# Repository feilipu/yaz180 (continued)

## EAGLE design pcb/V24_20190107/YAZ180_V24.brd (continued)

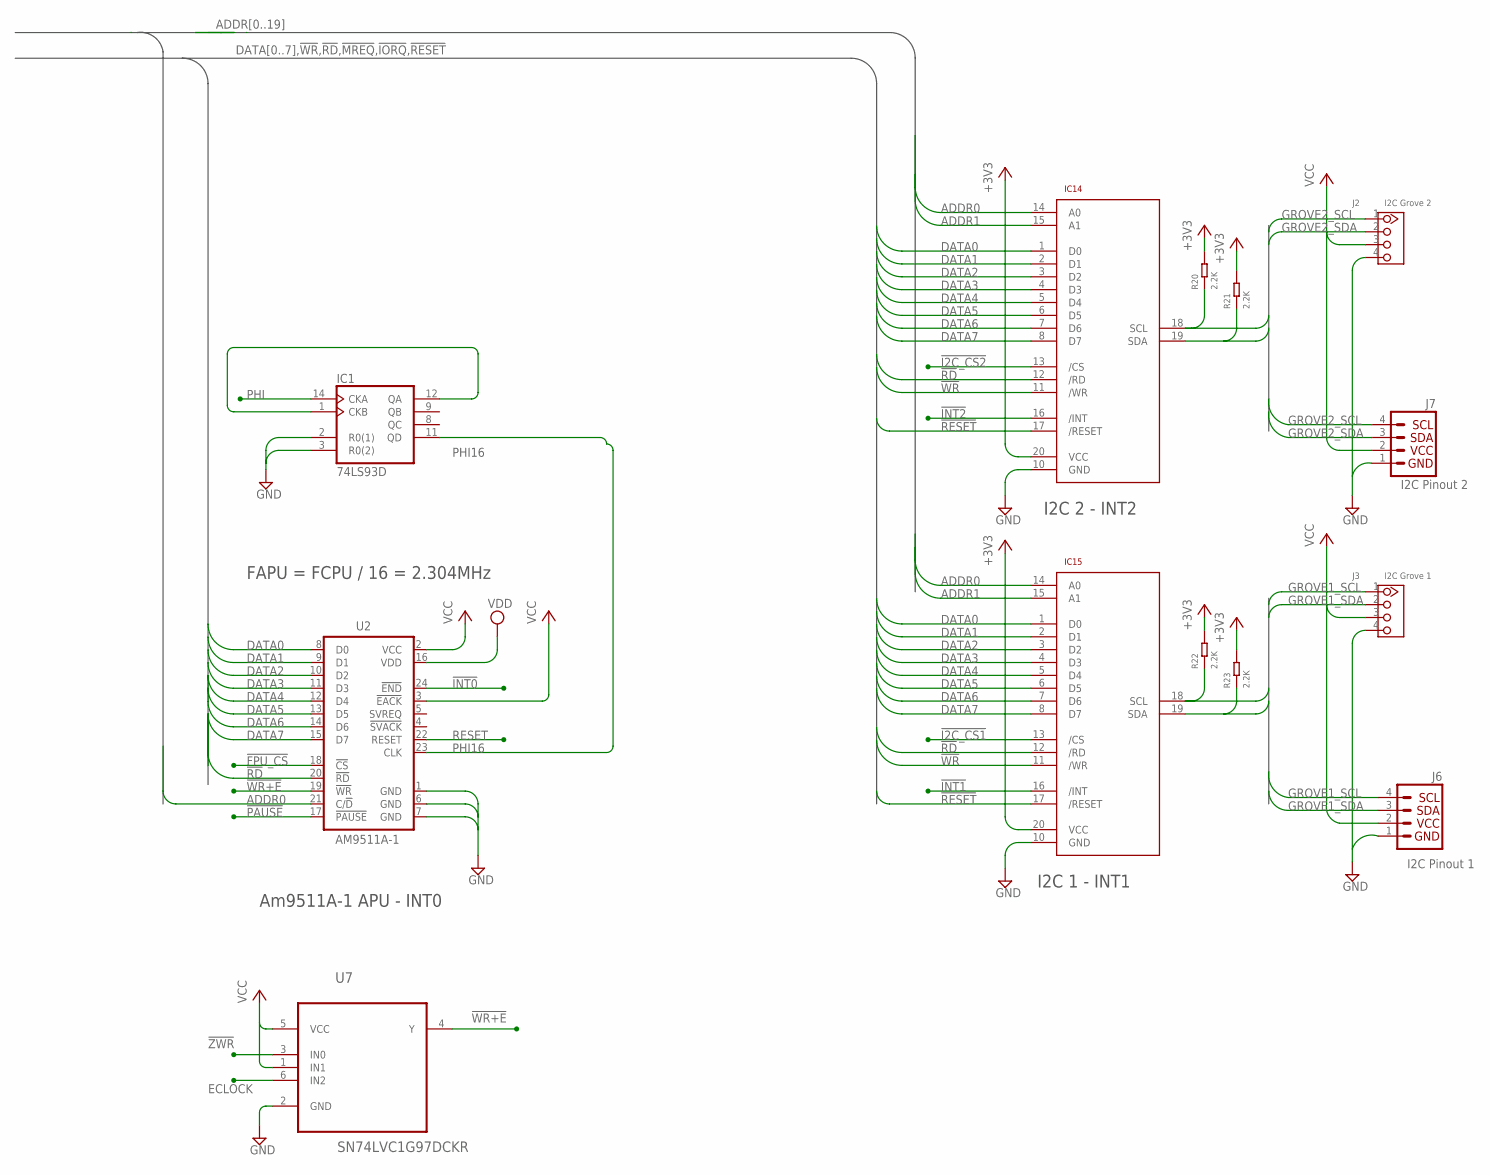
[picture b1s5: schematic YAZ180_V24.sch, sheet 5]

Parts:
IC1: 74LS93D; SO14
IC14, IC15: PCA9665; TSSOP20
J2: I2C Grove 2; HW4-2.0-90D
J3: I2C Grove 1; HW4-2.0-90D
J6: I2C Pinout 1; 1X04
J7: I2C Pinout 2; 1X04
R20, R21, R22, R23: 2.2K; R0603
U2: AM9511A-1; DIL24-6
U7: SN74LVC1G97DCKR; SOT65P210X110-6N

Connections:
!FPU_CS: U2.18 (!CS); also elsewhere on the board
!I2C_CS1: IC15.13 (/CS); also elsewhere on the board
!I2C_CS2: IC14.13 (/CS); also elsewhere on the board
!INT0: U2.24 (!END); also elsewhere on the board
!INT1: IC15.16 (/INT); also elsewhere on the board
!INT2: IC14.16 (/INT); also elsewhere on the board
!PAUSE: U2.17 (!PAUSE); also elsewhere on the board
!RD: IC14.12 (/RD), IC15.12 (/RD), U2.20 (!RD); also elsewhere on the board
!RESET: IC14.17 (/RESET), IC15.17 (/RESET); also elsewhere on the board
!WR: IC14.11 (/WR), IC15.11 (/WR); also elsewhere on the board
!WR+E: U2.19 (!WR), U7.4 (Y)
!ZWR: U7.3 (IN0); also elsewhere on the board
+3V3: IC14.20 (VCC), IC15.20 (VCC), R20.2, R21.2, R22.2, R23.2; also elsewhere on the board
ADDR0: IC14.14 (A0), IC15.14 (A0), U2.21 (C/!D); also elsewhere on the board
ADDR1: IC14.15 (A1), IC15.15 (A1); also elsewhere on the board
DATA0: IC14.1 (D0), IC15.1 (D0), U2.8 (D0); also elsewhere on the board
DATA1: IC14.2 (D1), IC15.2 (D1), U2.9 (D1); also elsewhere on the board
DATA2: IC14.3 (D2), IC15.3 (D2), U2.10 (D2); also elsewhere on the board
DATA3: IC14.4 (D3), IC15.4 (D3), U2.11 (D3); also elsewhere on the board
DATA4: IC14.5 (D4), IC15.5 (D4), U2.12 (D4); also elsewhere on the board
DATA5: IC14.6 (D5), IC15.6 (D5), U2.13 (D5); also elsewhere on the board
DATA6: IC14.7 (D6), IC15.7 (D6), U2.14 (D6); also elsewhere on the board
DATA7: IC14.8 (D7), IC15.8 (D7), U2.15 (D7); also elsewhere on the board
ECLOCK: U7.6 (IN2); also elsewhere on the board
GND: IC1.2 (R0(1)), IC1.3 (R0(2)), IC1.10 (GND), IC14.10 (GND), IC15.10 (GND), J2.4, J3.4, J6.1, J7.1, U2.1 (GND), U2.6 (GND), U2.7 (GND), U7.2 (GND); also elsewhere on the board
GROVE1_SCL: IC15.18 (SCL), J3.1, J6.4, R22.1
GROVE1_SDA: IC15.19 (SDA), J3.2, J6.3, R23.1
GROVE2_SCL: IC14.18 (SCL), J2.1, J7.4, R20.1
GROVE2_SDA: IC14.19 (SDA), J2.2, J7.3, R21.1
unnamed: IC1.1 (CKB), IC1.12 (QA)
PHI: IC1.14 (CKA); also elsewhere on the board
PHI16: IC1.11 (QD), U2.23 (CLK)
RESET: U2.22 (RESET); also elsewhere on the board
VCC: IC1.5 (VCC), J2.3, J3.3, J6.2, J7.2, U2.2 (VCC), U2.3 (!EACK), U7.1 (IN1), U7.5 (VCC); also elsewhere on the board
VDD: U2.16 (VDD); also elsewhere on the board

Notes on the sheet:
Am9511A-1 APU - INT0
I2C 2 - INT2
I2C 1 - INT1
FAPU = FCPU / 16 = 2.304MHz

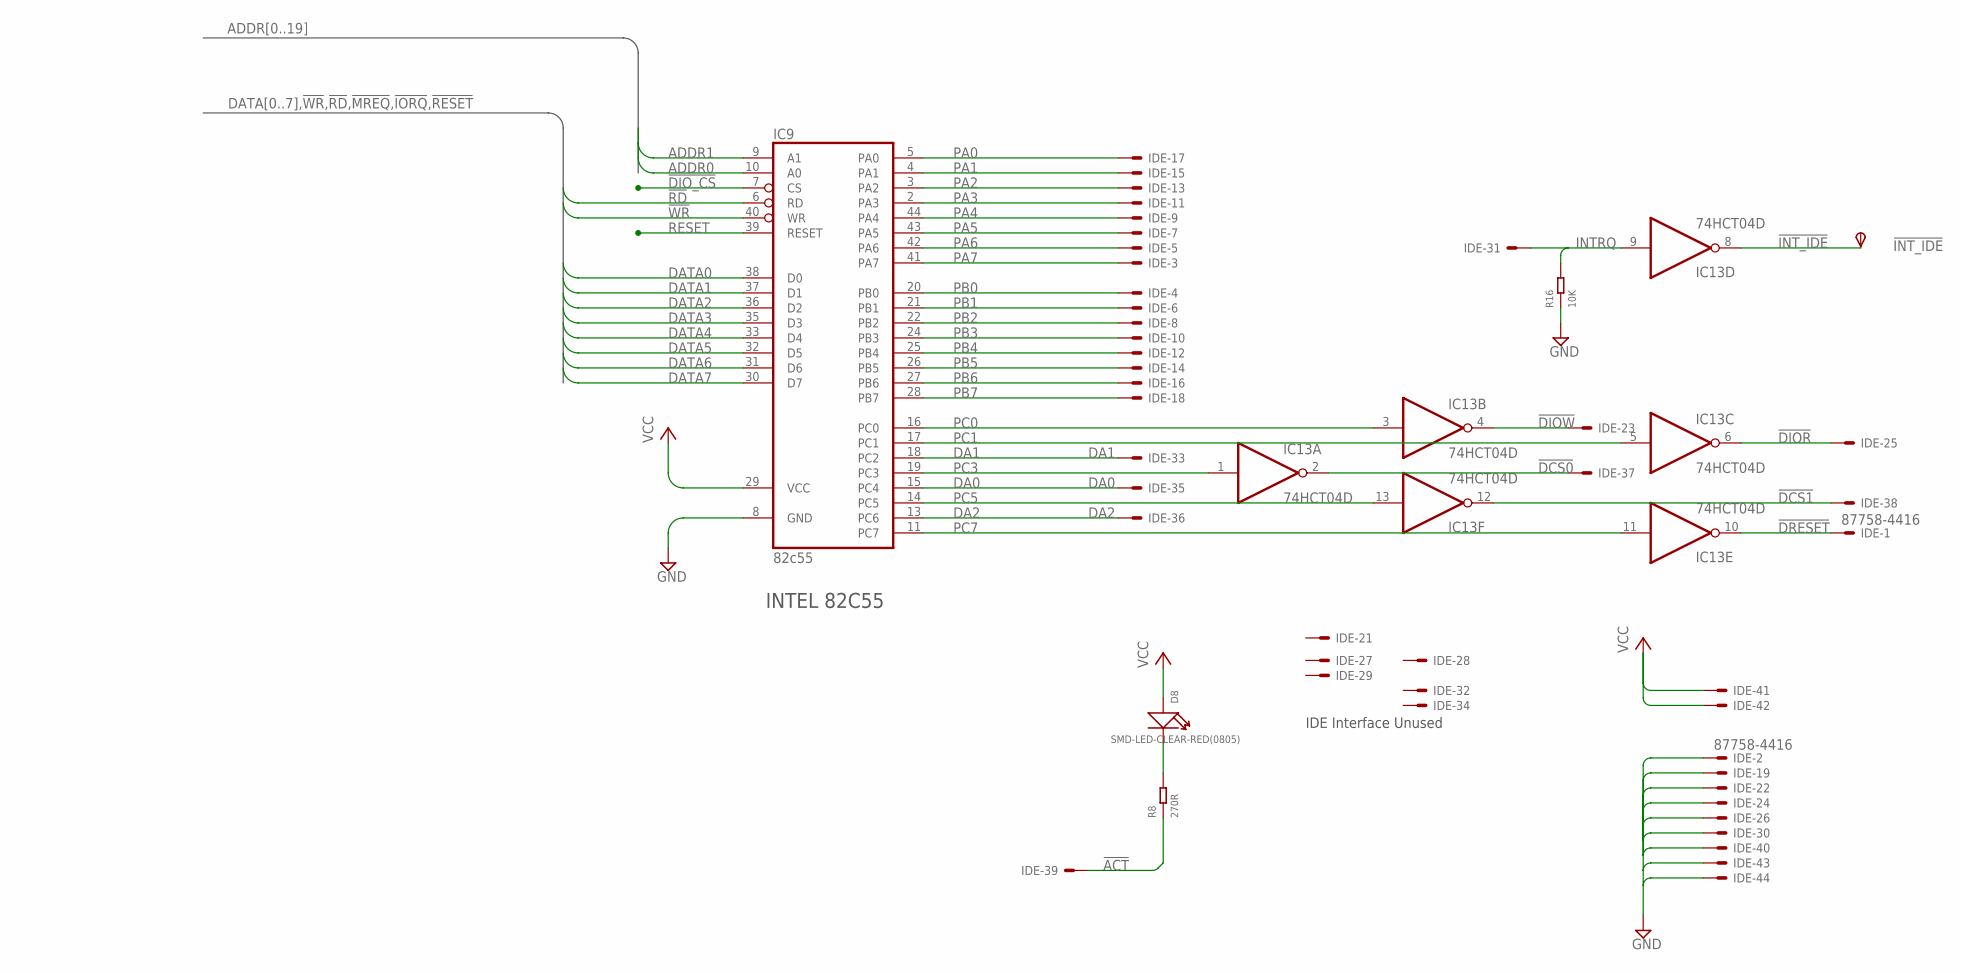
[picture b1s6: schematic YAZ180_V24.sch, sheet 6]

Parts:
!INT_IDE: TPSPAD1-13; P1-13
D8: SMD-LED-CLEAR-RED(0805); LED-0805
IC9: 82c55; S44
IC13: 74HCT04D; SO14
IDE: 87758-4416
R8: 270R; R0603
R16: 10K; R0603

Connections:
!ACT: IDE.39, R8.1
!DCS0: IC13.2 (O), IDE.37
!DCS1: IC13.12 (O), IDE.38
!DIOR: IC13.6 (O), IDE.25
!DIOW: IC13.4 (O), IDE.23
!DIO_CS: IC9.7 (CS); also elsewhere on the board
!DRESET: IC13.10 (O), IDE.1
!INT_IDE: !INT_IDE.TP, IC13.8 (O)
!RD: IC9.6 (RD); also elsewhere on the board
!WR: IC9.40 (WR); also elsewhere on the board
ADDR0: IC9.10 (A0); also elsewhere on the board
ADDR1: IC9.9 (A1); also elsewhere on the board
DA0: IC9.15 (PC4), IDE.35
DA1: IC9.18 (PC2), IDE.33
DA2: IC9.13 (PC6), IDE.36
DATA0: IC9.38 (D0); also elsewhere on the board
DATA1: IC9.37 (D1); also elsewhere on the board
DATA2: IC9.36 (D2); also elsewhere on the board
DATA3: IC9.35 (D3); also elsewhere on the board
DATA4: IC9.33 (D4); also elsewhere on the board
DATA5: IC9.32 (D5); also elsewhere on the board
DATA6: IC9.31 (D6); also elsewhere on the board
DATA7: IC9.30 (D7); also elsewhere on the board
GND: IC9.8 (GND), IC13.7 (GND), IDE.2, IDE.19, IDE.22, IDE.24, IDE.26, IDE.30, IDE.40, IDE.43, IDE.44, R16.1; also elsewhere on the board
INTRQ: IC13.9 (I), IDE.31, R16.2
unnamed: D8.-, R8.2
PA0: IC9.5 (PA0), IDE.17
PA1: IC9.4 (PA1), IDE.15
PA2: IC9.3 (PA2), IDE.13
PA3: IC9.2 (PA3), IDE.11
PA4: IC9.44 (PA4), IDE.9
PA5: IC9.43 (PA5), IDE.7
PA6: IC9.42 (PA6), IDE.5
PA7: IC9.41 (PA7), IDE.3
PB0: IC9.20 (PB0), IDE.4; also elsewhere on the board
PB1: IC9.21 (PB1), IDE.6; also elsewhere on the board
PB2: IC9.22 (PB2), IDE.8; also elsewhere on the board
PB3: IC9.24 (PB3), IDE.10; also elsewhere on the board
PB4: IC9.25 (PB4), IDE.12; also elsewhere on the board
PB5: IC9.26 (PB5), IDE.14; also elsewhere on the board
PB6: IC9.27 (PB6), IDE.16; also elsewhere on the board
PB7: IC9.28 (PB7), IDE.18; also elsewhere on the board
PC0: IC9.16 (PC0), IC13.3 (I)
PC1: IC9.17 (PC1), IC13.5 (I); also elsewhere on the board
PC3: IC9.19 (PC3), IC13.1 (I)
PC5: IC9.14 (PC5), IC13.13 (I)
PC7: IC9.11 (PC7), IC13.11 (I)
RESET: IC9.39 (RESET); also elsewhere on the board
VCC: D8.+, IC9.29 (VCC), IC13.14 (VCC), IDE.41, IDE.42; also elsewhere on the board

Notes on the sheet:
INTEL 82C55
IDE Interface Unused

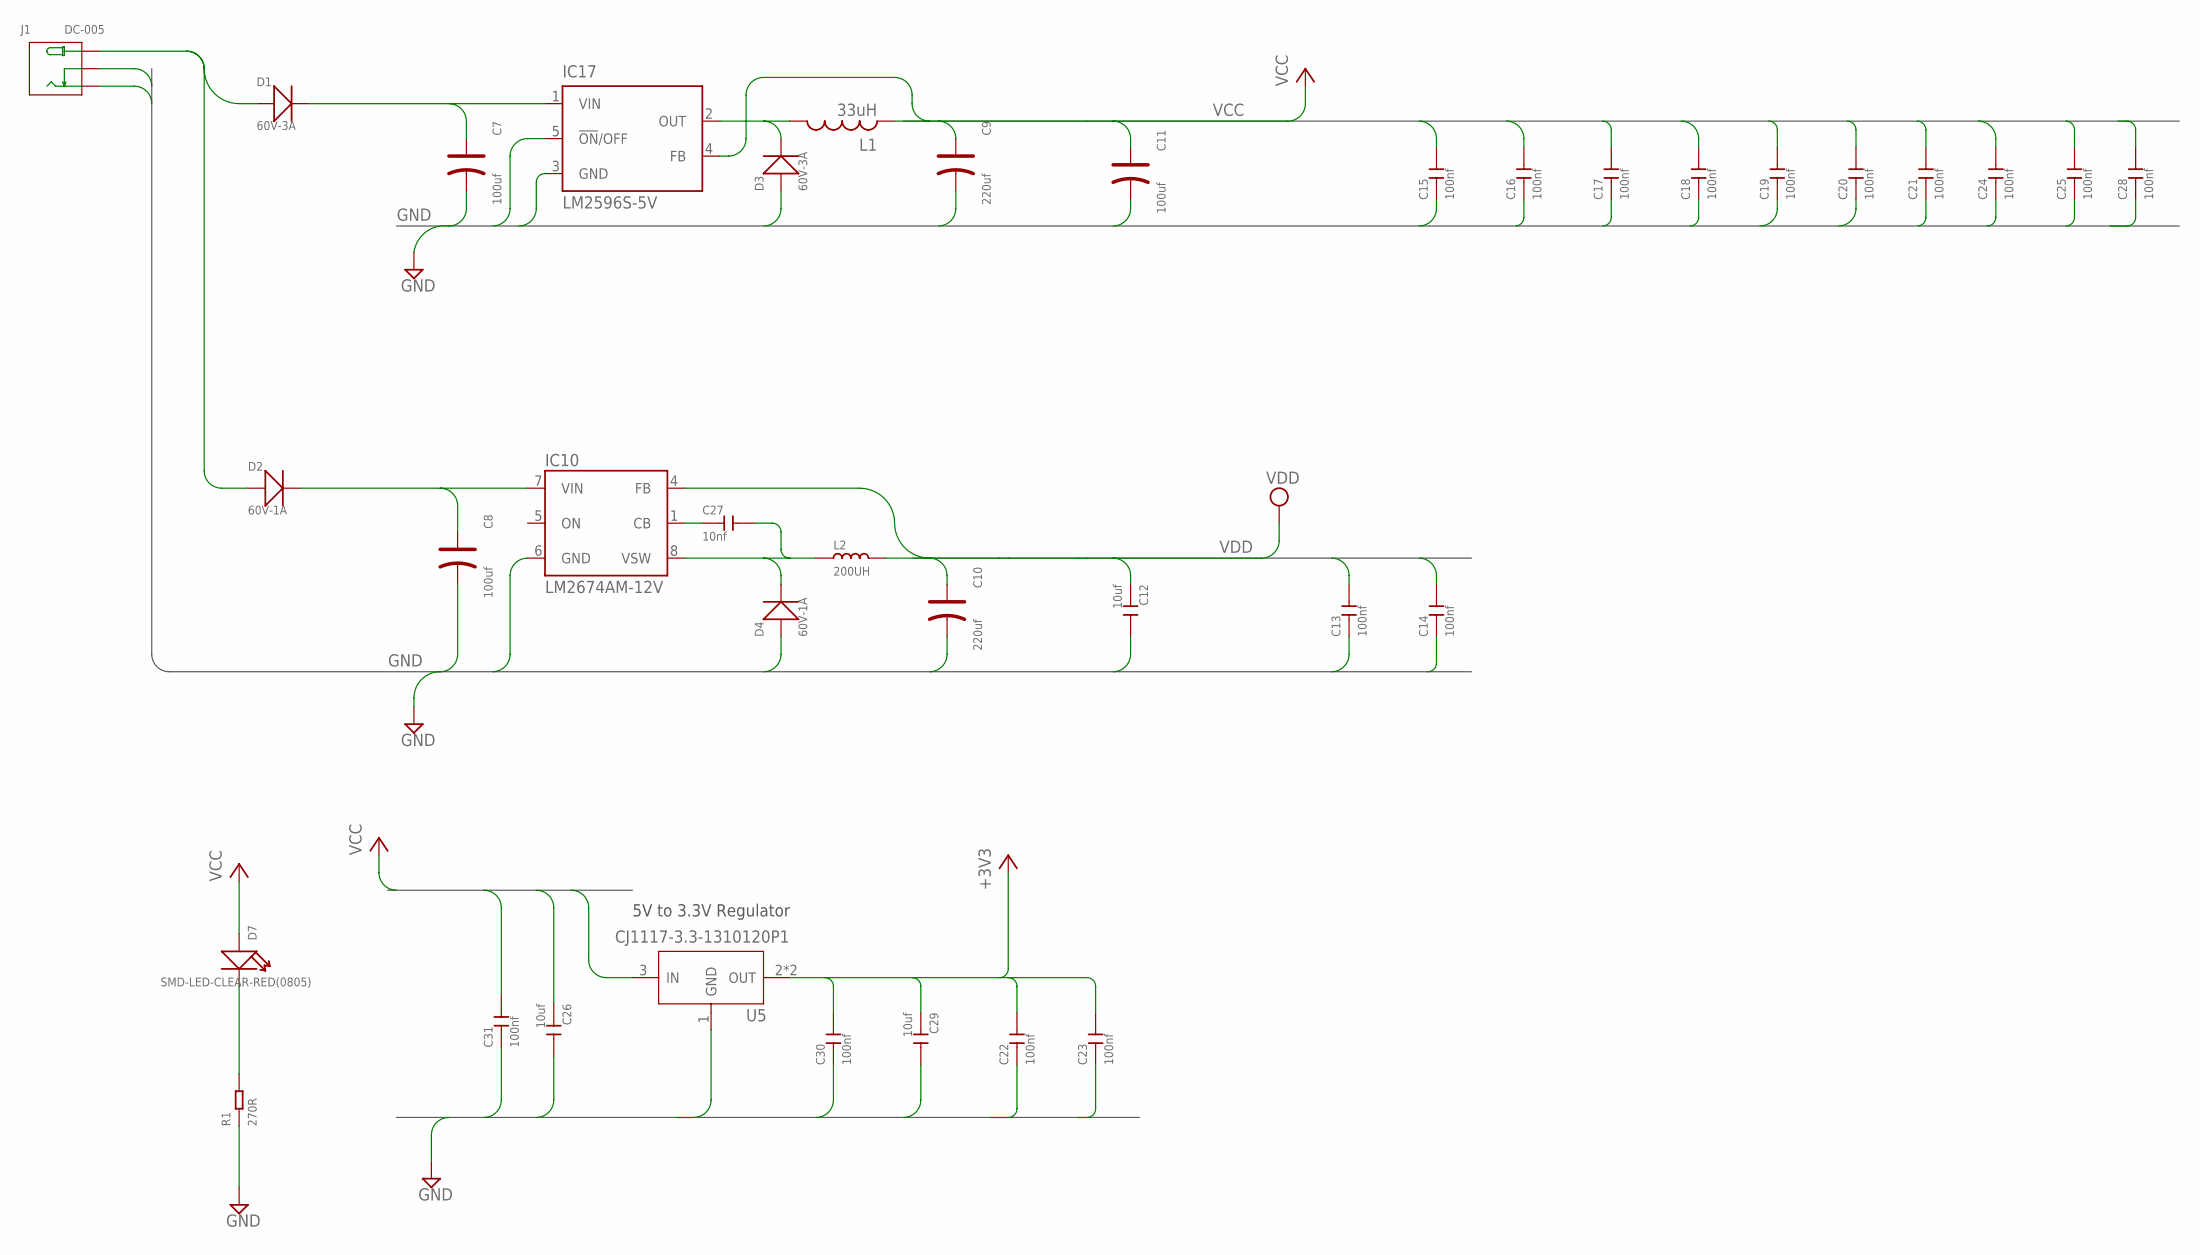
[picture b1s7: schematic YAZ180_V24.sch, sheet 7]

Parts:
C7, C8: 100uf; ELECTRO-SMD-E-7.8MM
C9, C10: 220uf; AVX-E
C11: 100uf; AVX-C
C12, C26, C29: 10uf; C0805
C13, C14, C15, C16, C17, C18, C19, C20, C21, C22, C23, C24, C25, C28, C30, C31: 100nf; C0603
C27: 10nf; C0603
D1, D3: 60V-3A; SOD-323
D2, D4: 60V-1A; SOD-323
D7: SMD-LED-CLEAR-RED(0805); LED-0805
IC10: LM2674AM-12V; SO08
IC17: LM2596S-5V; TO263-5
J1: DC-005; DCJ3P-14.2X11.0X9.0MM
L1: 33uH; MSS1260
L2: 200UH; SMD-2P-5.0X5.0X2.0MM
R1: 270R; R0603
U5: CJ1117-3.3-1310120P1; SOT89

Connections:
+3V3: C22.2, C23.2, C29.1, C30.2, U5.2 (OUT), U5.4 (OUT); also elsewhere on the board
GND: C7.-, C8.-, C9.-, C10.-, C11.-, C12.2, C13.1, C14.1, C15.1, C16.1, C17.1, C18.1, C19.1, C20.1, C21.1, C22.1, C23.1, C24.1, C25.1, C26.2, C28.1, C29.2, C30.1, C31.1, D3.+, D4.+, IC10.6 (GND), IC17.3 (GND), IC17.5 (!ON!/OFF), J1.-1 (-), J1.-2 (CDN), R1.1, U5.1 (GND); also elsewhere on the board
unnamed: C27.1, IC10.1 (CB)
unnamed: D1.+, D2.+, J1.+
unnamed: D7.-, R1.2
unnamed: C7.+, D1.-, IC17.1 (VIN)
unnamed: C8.+, D2.-, IC10.7 (VIN)
unnamed: D3.-, IC17.2 (OUT), L1.P$1
unnamed: C27.2, D4.-, IC10.8 (VSW), L2.1
VCC: C9.+, C11.+, C15.2, C16.2, C17.2, C18.2, C19.2, C20.2, C21.2, C24.2, C25.2, C26.1, C28.2, C31.2, D7.+, IC17.4 (FB), L1.P$2, U5.3 (IN); also elsewhere on the board
VDD: C10.+, C12.1, C13.2, C14.2, IC10.4 (FB), L2.2; also elsewhere on the board

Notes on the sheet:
5V to 3.3V Regulator

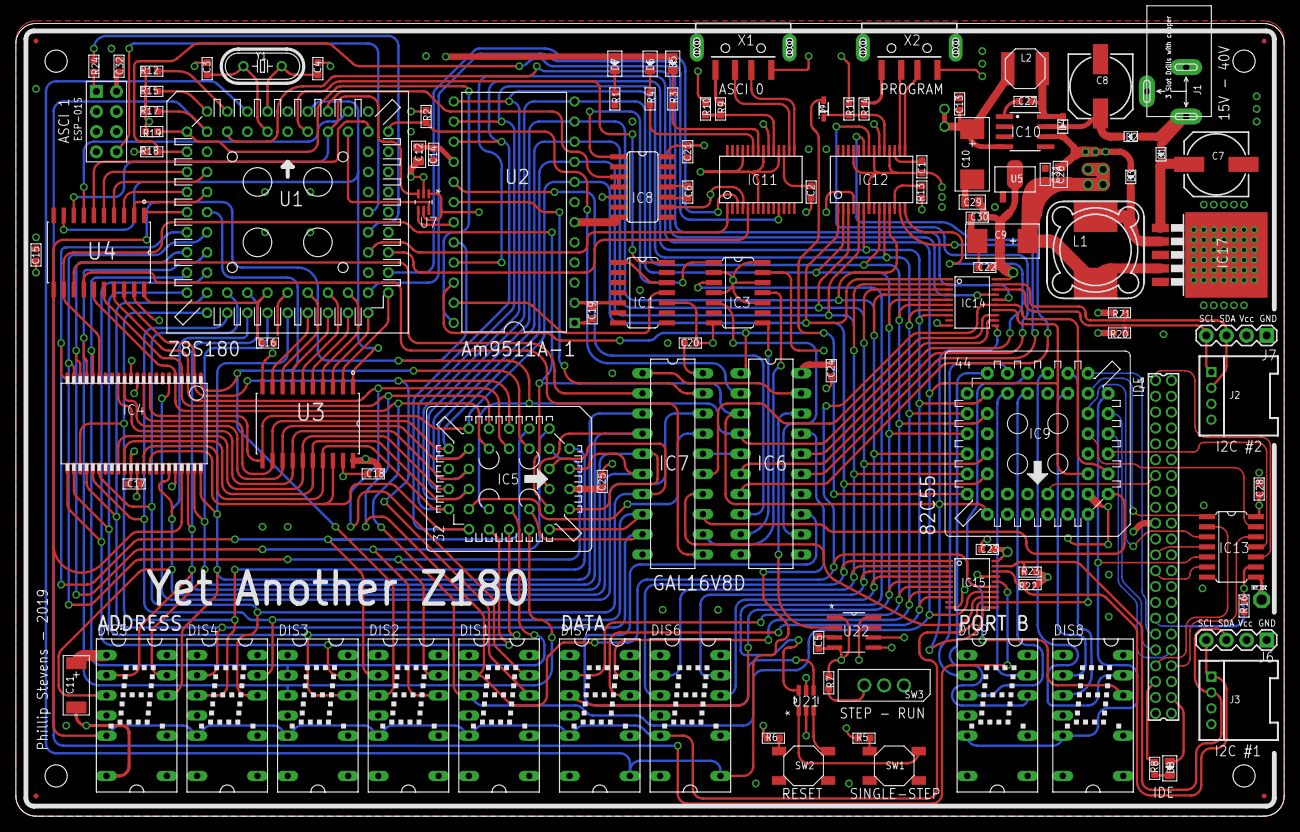
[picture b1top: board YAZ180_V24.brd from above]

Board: 4 copper layers, 160.0 x 100.0 mm, 117 parts (0 on the bottom side), 163 nets.

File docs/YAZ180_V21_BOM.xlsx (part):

Part | Value | Device | Package | Description | MF | MPN | OC_FARNELL | OC_NEWARK | PACKAGE | SUPPLIER | TP_SIGNAL_NAME | VALUE
!INT_IDE | TPSPAD1-13 | TPSPAD1-13 | P1-13 | TEST PIN
C1 | 100nf | CERAMIC-100NF-50V-10%-X7R(0603) | C0603 | 302010138 |  | CC0603KRX7R9BB104 |  |  |  |  |  | 100nf
C2 | 100nf | CERAMIC-100NF-50V-10%-X7R(0603) | C0603 | 302010138 |  | CC0603KRX7R9BB104 |  |  |  |  |  | 100nf
C3 | 22pf | CERAMIC-22PF-50V-5%-NPO(0603) | C0603 | 302010143 |  |  |  |  |  |  |  | 22pf
C4 | 22pf | CERAMIC-22PF-50V-5%-NPO(0603) | C0603 | 302010143 |  |  |  |  |  |  |  | 22pf
C5 | 2.2uf | CERAMIC-2.2UF-10V-10%-X7R(0603) | C0603 | 302010054 |  | CC0603KRX7R6BB225 |  |  |  |  |  | 2.2uf
C6 | 22pf | CERAMIC-22PF-50V-5%-NPO(0603) | C0603 | 302010143 |  |  |  |  |  |  |  | 22pf
C7 | 100uf | ALUMINUM-SMD-100UF-50V(D8-H10.5MM) | ELECTRO-SMD-E-7.8MM | 302030095 |  | CS1H101M-CRF10 |  |  |  |  |  | 100uf
C8 | 100uf | ALUMINUM-SMD-100UF-50V(D8-H10.5MM) | ELECTRO-SMD-E-7.8MM | 302030095 |  | CS1H101M-CRF10 |  |  |  |  |  | 100uf
C9 | 220uf | TANTALUM-SMD-220UF-16V(AVX-E) | AVX-E | 302020032 |  | TAJE227K016RNJ |  |  |  |  |  | 220uf
C10 | 220uf | TANTALUM-SMD-220UF-16V(AVX-E) | AVX-E | 302020032 |  | TAJE227K016RNJ |  |  |  |  |  | 220uf
C11 | 100uf | TANTALUM-SMD-100UF-16V(AVX-C) | AVX-C | 302020023 |  | TAJC107K016RNJ |  |  |  |  |  | 100uf
C12 | 10uf | CERAMIC-10UF-25V-10%-X5R(0805) | C0805 | 302010178 |  | CC0805KKX5R8BB106 |  |  |  |  |  | 10uf
C13 | 100nf | CERAMIC-100NF-50V-10%-X7R(0603) | C0603 | 302010138 |  | CC0603KRX7R9BB104 |  |  |  |  |  | 100nf
C14 | 100nf | CERAMIC-100NF-50V-10%-X7R(0603) | C0603 | 302010138 |  | CC0603KRX7R9BB104 |  |  |  |  |  | 100nf
C15 | 100nf | CERAMIC-100NF-50V-10%-X7R(0603) | C0603 | 302010138 |  | CC0603KRX7R9BB104 |  |  |  |  |  | 100nf
C16 | 100nf | CERAMIC-100NF-50V-10%-X7R(0603) | C0603 | 302010138 |  | CC0603KRX7R9BB104 |  |  |  |  |  | 100nf
C17 | 100nf | CERAMIC-100NF-50V-10%-X7R(0603) | C0603 | 302010138 |  | CC0603KRX7R9BB104 |  |  |  |  |  | 100nf
C18 | 100nf | CERAMIC-100NF-50V-10%-X7R(0603) | C0603 | 302010138 |  | CC0603KRX7R9BB104 |  |  |  |  |  | 100nf
C19 | 100nf | CERAMIC-100NF-50V-10%-X7R(0603) | C0603 | 302010138 |  | CC0603KRX7R9BB104 |  |  |  |  |  | 100nf
C20 | 100nf | CERAMIC-100NF-50V-10%-X7R(0603) | C0603 | 302010138 |  | CC0603KRX7R9BB104 |  |  |  |  |  | 100nf
C21 | 100nf | CERAMIC-100NF-50V-10%-X7R(0603) | C0603 | 302010138 |  | CC0603KRX7R9BB104 |  |  |  |  |  | 100nf
C22 | 100nf | CERAMIC-100NF-50V-10%-X7R(0603) | C0603 | 302010138 |  | CC0603KRX7R9BB104 |  |  |  |  |  | 100nf
C23 | 100nf | CERAMIC-100NF-50V-10%-X7R(0603) | C0603 | 302010138 |  | CC0603KRX7R9BB104 |  |  |  |  |  | 100nf
C24 | 100nf | CERAMIC-100NF-50V-10%-X7R(0603) | C0603 | 302010138 |  | CC0603KRX7R9BB104 |  |  |  |  |  | 100nf
C25 | 100nf | CERAMIC-100NF-50V-10%-X7R(0603) | C0603 | 302010138 |  | CC0603KRX7R9BB104 |  |  |  |  |  | 100nf
C26 | 10uf | CERAMIC-10UF-25V-10%-X5R(0805) | C0805 | 302010178 |  | CC0805KKX5R8BB106 |  |  |  |  |  | 10uf
C27 | 10nf | CERAMIC-10NF-50V-10%-X7R(0603) | C0603 | 302010140 |  | CC0603KRX7R9BB103 |  |  |  |  |  | 10nf
C28 | 100nf | CERAMIC-100NF-50V-10%-X7R(0603) | C0603 | 302010138 |  | CC0603KRX7R9BB104 |  |  |  |  |  | 100nf
C29 | 10uf | CERAMIC-10UF-25V-10%-X5R(0805) | C0805 | 302010178 |  | CC0805KKX5R8BB106 |  |  |  |  |  | 10uf
C30 | 100nf | CERAMIC-100NF-50V-10%-X7R(0603) | C0603 | 302010138 |  | CC0603KRX7R9BB104 |  |  |  |  |  | 100nf
C31 | 100nf | CERAMIC-100NF-50V-10%-X7R(0603) | C0603 | 302010138 |  | CC0603KRX7R9BB104 |  |  |  |  |  | 100nf
C32 | 100nf | CERAMIC-100NF-50V-10%-X7R(0603) | C0603 | 302010138 |  | CC0603KRX7R9BB104 |  |  |  |  |  | 100nf
C33 | 100nf | CERAMIC-100NF-50V-10%-X7R(0603) | C0603 | 302010138 |  | CC0603KRX7R9BB104 |  |  |  |  |  | 100nf
D1 | 60V-3A | SMD-DIODE-SCHOTTKY-60V-1A(SOD-323) | SOD-323 | 304020026 |  | PMEG6010CEJ,115 |  |  |  |  |  | 60V-1A
D2 | 60V-1A | SMD-DIODE-SCHOTTKY-60V-1A(SOD-323) | SOD-323 | 304020026 |  | PMEG6010CEJ,115 |  |  |  |  |  | 60V-1A
D3 | 60V-3A | SMD-DIODE-SCHOTTKY-60V-1A(SOD-323) | SOD-323 | 304020026 |  | PMEG6010CEJ,115 |  |  |  |  |  | 60V-1A
D4 | 60V-1A | SMD-DIODE-SCHOTTKY-60V-1A(SOD-323) | SOD-323 | 304020026 |  | PMEG6010CEJ,115 |  |  |  |  |  | 60V-1A
D5 | SMD-LED-CLEAR-YELLOW(0805) | SMD-LED-CLEAR-YELLOW(0805) | LED-0805 | 304090039 |  | 17-215UYC/S530-A3/TR8
D6 | SMD-LED-CLEAR-GREEN(0805) | SMD-LED-CLEAR-GREEN(0805) | LED-0805 | 304090057 |  | 17-215SYGC/S530-E2/TR8
D7 | SMD-LED-CLEAR-RED(0805) | SMD-LED-CLEAR-RED(0805) | LED-0805 | 304090046 |  | 17-215SURC/S530-A2/TR8
D8 | SMD-LED-CLEAR-RED(0805) | SMD-LED-CLEAR-RED(0805) | LED-0805 | 304090046 |  | 17-215SURC/S530-A2/TR8
DIS1 | HTIL311A | HTIL311A | HTIL311A | LED DISPLAY 1-character dot matrix, 2 decimal points |  |  | unknown | unknown
DIS2 | HTIL311A | HTIL311A | HTIL311A | LED DISPLAY 1-character dot matrix, 2 decimal points |  |  | unknown | unknown
DIS3 | HTIL311A | HTIL311A | HTIL311A | LED DISPLAY 1-character dot matrix, 2 decimal points |  |  | unknown | unknown
DIS4 | HTIL311A | HTIL311A | HTIL311A | LED DISPLAY 1-character dot matrix, 2 decimal points |  |  | unknown | unknown
DIS5 | HTIL311A | HTIL311A | HTIL311A | LED DISPLAY 1-character dot matrix, 2 decimal points |  |  | unknown | unknown
DIS6 | HTIL311A | HTIL311A | HTIL311A | LED DISPLAY 1-character dot matrix, 2 decimal points |  |  | unknown | unknown
DIS7 | HTIL311A | HTIL311A | HTIL311A | LED DISPLAY 1-character dot matrix, 2 decimal points |  |  | unknown | unknown
DIS8 | HTIL311A | HTIL311A | HTIL311A | LED DISPLAY 1-character dot matrix, 2 decimal points |  |  | unknown | unknown
DIS9 | HTIL311A | HTIL311A | HTIL311A | LED DISPLAY 1-character dot matrix, 2 decimal points |  |  | unknown | unknown
ESP-01S | ESP-01S | DIP-BLACK-FEMALE-HEADER(2X4P-2.54) | H2X4-2.54 | 320030087 |  |  |  |  |  |  |  | 2X4P-2.54
IC1 | 74LS93D | 74LS93D | SO14 | Decade, divide by twelve and binary COUNTER
IC3 | 74ACT74D | 74ACT74D | SO14 | Dual D type positive edge triggered FLIP FLOP, preset and clear
IC4 | IS62WV10248DALL-55T | IS62WV10248DALL-55T | TSOP-II-44 | 1024k x 8 low voltage, ultra low power CMOS static RAM
IC5 | SST39VF010 | SST39VF010 | S32 | 1 Mbit x8 Multi-Purpose Flash
IC6 | ATF16V8BP3 | ATF16V8BP3 | DIL20 | High perfomance CMOS (electrically erasable) programmable logic device (PLD) |  | ATF16V8CZ-15PU | 1551768 | 94M6254
IC7 | ATF16V8BP3 | ATF16V8BP3 | DIL20 | High perfomance CMOS (electrically erasable) programmable logic device (PLD) |  | ATF16V8CZ-15PU | 1551768 | 94M6254
IC8 | 74121D | 74121D | SO14 | Monostable MULTIVIBRATOR, schmitt trigger inputs
IC9 | 82c55 | 82C55APLCC44-S | S44 | MICROCOMPUTER/PERIPHERAL DEVICE
IC10 | LM2674AM-12V | LM2674AM | SO08 | National Semiconductor 0.5A Simple Switcher"(c)"
IC11 | FT232RL | FT232RL | SSOP28DB | USB UART
IC12 | FT245RL | FT245RL | SSOP28DB | USB FIFO Controller
IC13 | 74HCT04D | 74HCT04D | SO14 | Hex INVERTER
IC14 | PCA9665 | PCA9665 | TSSOP20 | IC CNTRLR PARALLEL/I2C 20TSSOP
IC15 | PCA9665 | PCA9665 | TSSOP20 | IC CNTRLR PARALLEL/I2C 20TSSOP
IC17 | LM2596S-5V | LM2596S | TO263-5 | SIMPLE SWITCHERÂ® Power Converter 150 kHz 3A Step-Down Voltage Regulator | NATIONAL SEMICONDUCTOR | LM2596S-ADJ/NOPB | 9494367 | 41K3842
IDE | 87758-4416 | 87758-4416 | 87758-4416 | 44 Pin - 2mm Dual Row Single Wafer, Vertical T/H HDR | MOLEX | 87758-4416 | unknown | 59J1588
J1 | DC-005 | CONN-POWER-JACK-2.1MM(DC-005) | DCJ3P-14.2X11.0X9.0MM | 320120003 |  | DC-005 |  |  |  |  |  | DC-005
J2 | I2C Grove 2 | GROVE-CONNECTOR-DIP-90D(4P-2.0) | HW4-2.0-90D | 320110034
J3 | I2C Grove 1 | GROVE-CONNECTOR-DIP-90D(4P-2.0) | HW4-2.0-90D | 320110034
J6 | I2C Pinout 1 | I2C_STANDARD | 1X04 | SparkFun has standardized on a pinout for all I2C based sensor breakouts.
J7 | I2C Pinout 2 | I2C_STANDARD | 1X04 | SparkFun has standardized on a pinout for all I2C based sensor breakouts.
L1 | 33uH | MSS1260 | MSS1260 | SMT Power Inductor
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
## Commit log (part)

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2017-10-13 initial structure + documents
2017-10-13 add APU and update readme
2017-10-13 add readme image refs
2017-10-13 update docs memory & page 0
2017-10-13 update doc page 0
2017-10-15 yabios readme
2017-10-16 yabios readme.md update
2017-10-17 squash CA1 to 4kB
2017-10-18 remove double underscore
2017-10-23 implementation notes
2017-10-26 rethink bank address implementation
2017-10-26 update readme with far improvements
2017-10-29 update readme & notes
2017-10-29 update Page0 doc
2017-10-29 rename _memcpy_far & _memset_far
2017-10-30 revise memcpy_far and memset_far definitions
2017-10-31 Excel Version of BOM
    Includes stock in hand on 1 Nov 2017
2017-10-31 Digikey Shopping Cart
    Final V2.1 shopping cart at Digikey.
    In case the Internet forgets.
2017-10-31 readme updates
2017-11-01 initial yash implementation
2017-11-01 wip - CLI mostly done
2017-11-02 wip - shell complete excluding bank functions
2017-11-02 wip - check more boxes
2017-11-02 CLI is alive
2017-11-02 wip - last before banked integration
2017-11-03 mkb & mvb
2017-11-07 Working State - Melbourne Cup
2017-11-18 update images and readme
2017-11-18 update Tindie link
2017-11-18 add Tindie badge
2017-11-19 WIP - add perl z180tool
2017-11-25 create yabios.rex for API
2017-11-26 recompile with zsdcc 10186
2017-11-27 updates, compiling with zsdcc-9958
2017-11-30 halved Tx buffer size
2017-12-10 cpm22 ccp+bdos initial commit
2017-12-15 Update README.MD
    CP/M tick-box
2017-12-15 move IDE support to Common Area 1 for CP/M
2017-12-16 yabios03 hex file
2018-01-13 yabios CP/M WIP
2018-01-13 yabios CP/M WIP2
2018-01-14 CP/M WIP
2018-01-15 yabios - CP/M disks working
2018-01-17 yabios - working CP/M flash boot
2018-01-18 CP/M flash fixes
2018-01-18 CP/M flash fixes in BIOS
2018-01-22 CP/M disk WIP
2018-01-24 CP/M disks working
2018-01-24 readme and comment tidy
2018-01-29 CP/M LBA optimisation & polish
2018-01-30 recover 0x100 bytes & polish
2018-01-31 fix mkcpmb and CP/M wboot SP
2018-01-31 CP/M CCP/BDOS polishing
2018-01-31 update readme - release yabios04
2018-02-01 update CUPL PLD descriptions
2018-02-01 update readme with new CUPL and polishing
2018-02-04 remove obsolete memory layout
2018-02-04 add revised memory mapping
2018-02-04 update readme for memory realignment
2018-02-04 YAZ180 CP/M example
2018-02-05 refreshed ff & time libraries
2018-02-22 check existence of CP/M drive before selecting
2018-02-22 check existence of CP/M drive before selecting - 2
2018-02-22 check existence of CP/M drive before selecting - 3
2018-02-22 check existence of CP/M drive before selecting - 4
2018-02-23 Added PCB Version 2.2
2018-02-23 Removed old V2.1 directory
2018-02-23 check existence of CP/M drive before selecting - 5
2018-02-26 optimise BIOS 16 bit adds
2018-02-26 align BDOS to page
2018-02-28 revised z88dk terminal drivers
2018-03-01 use getline()
2018-03-01 clean up yabios.def
2018-03-02 rebuild with correct asci config
2018-03-04 enable HEX loading via asci1
2018-03-04 constantify some strings
2018-03-04 recompiled
2018-03-04 ux improvements
2018-03-08 select serial port
2018-03-09 add EXIT command
2018-03-10 recompile
2018-03-11 update notes
2018-03-11 PCBv2.1 Errata
2018-03-11 PCBv2_ESP_pins
2018-03-11 update errata
2018-03-12 info update
2018-03-13 fix stack collision
2018-03-15 OCD stack_canary -> delete memset_far
2018-03-18 various whitespace
2018-03-24 minor updates from RC2014 work
2018-03-24 include updates from rc2014 CP/M
2018-03-24 add LBA references on CP/M
2018-03-26 recompile with zsdcc #9958 Mar 26
2018-03-28 Error if f_opendir() fails
2018-05-07 yabios - extracted from z88dk
2018-05-07 keep stack safe during initialisation
2018-05-07 allow two part user crt_preamble
2018-05-09 yabios07 - segregated from z88dk
2018-05-09 yabios 07 release
2018-05-10 recent photographs
2018-05-10 v2.2 PCB image
2018-05-18 yabios - ChaN FATFS Version 13b & CA1 Drivers 0xF580
2018-05-18 yabios - update version
2018-05-20 yabios - sizeof oops
2018-05-22 minor cleanups
2018-05-27 CP/M - adjust wboot
2018-05-27 CP/M - minor stack issue
2018-06-03 yabios - bank aware apu driver
2018-06-05 yabios - fix APU device driver
2018-06-06 CP/M - revert delete serial flush
2018-06-07 yabios - pchar to yabios def
2018-06-30 yabios - with z180 mlt
2018-07-07 yabios - v1.0 release
2018-07-07 v11 - apu optimise
2018-07-18 hardware - APU Reset
2018-07-18 hardware - APU Reset png
2018-07-22 CP/M - support XMODEM
2018-07-22 CP/M - add drive files
2018-07-29 CP/M - BDOS simple JP optimisation
2018-07-29 CP/M - whitespace
2018-07-29 CP/M - BDOS error optimisation
2018-08-07 CP/M Updated MLOAD to v2.5
2018-08-11 yabios - FatFS v13b Patch 2
2018-08-11 yabios - heap to 8kB
2018-08-13 yabios - ASCI1 TTY to 9600 8n2 default
2018-08-19 CP/M - working BASCOM
2018-08-31 yabios - Turbo mode 36.864MHz
2018-08-31 yabios - Turbo mode 36.864MHz clock
2018-09-02 cp/m - mp/m deblocking
2018-09-04 yabios - update README.MD
2018-09-09 mpm21 - initial commit
2018-09-13 cpm22 - Hi-Tech C
2018-09-14 YAZ180 - build documents
2018-09-14 YAZ180 - construction notes update
2018-09-15 CP/M - Hi-Tech C Libraries
2018-09-15 Update construction_notes.md to clarify modification.
2018-09-22 YAZ180 - Hi-Tech C library header update
2018-09-22 yabios - recompile z80asm v13 & peephole fix
2018-09-23 docs - v2.1 with modifications
2018-09-23 docs - construction notes
2018-09-25 Owners Notes added
2018-09-28 yabios - FatFS v13b Patch 3
2018-09-28 mpm21 - progress with C mpmldr
2018-09-29 MP/M - mpmldr for debug
2018-09-29 MP/M - mpmldr adjust assembly glue
2018-09-30 MP/M - mpmldr reversed records, not bytes - working
2018-09-30 MP/M - mpmldr polish - pending jp_far
2018-09-30 yabios - rename _asci* to asm_asci*
2018-09-30 yabios - bank_get_rel() fix
2018-09-30 mpmldr - remove bank_get_rel fudge
2018-10-01 mpmldr - used after free
2018-10-08 mpm21 - WIP
2018-11-03 MP/M - WIP
2018-11-03 YAZ180 - Rework for Single Step
2018-11-11 yabios - ZSDCC Version 3.8.2 #10646
2018-11-20 YAZ180 - V2.3 for 2019 release
2018-11-20 YAZ180 - update construction notes for V2.3
2018-11-22 YAZ180 PCB V23 - Re-Gerbered for Seeed
2018-11-23 YAZ180 PCB V23 - Re-Gerbered again for Seeed
2018-12-08 revert to ZSDCC r9958
2018-12-12 docs - update BOM for V2.3
2018-12-14 yabios - recompile zsdcc 3.8.4
2019-01-07 PCB - V2.4 minor polishing
2019-01-09 PCB - V2.4 documents
2019-01-09 yabios - recompile with zsdcc r10854
2019-01-11 yabios - FatFS v13c.p2
2019-01-12 yabios - fix ya_pwd & ya_chmod
2019-01-31 yabios - recompile with zsdcc r10892
2019-02-01 CUPL - PCBv2.4 & SST39SF020A 256kB
2019-02-03 PCB - delete names from silk
2019-02-03 DOCS - v24 pictures
2019-02-03 README - update notes
2019-02-06 yabios - Version 1.2 Release
2019-02-06 YAZ180 - release 1.2
2019-02-06 YAZ180 - Release Notes Version 1.2
2019-02-06 YAZ180 - Release Notes fixes
2019-02-07 z180tool - update FTDI IDs
2019-02-08 yabios - add v1.2 HEX
2019-02-08 src - add mandelbrot test code
2019-02-08 app - rename app src directory
2019-03-26 yabios - zsdcc r11145 - 32GB recompile
2019-05-11 yabios - recompile zsdcc 3.9.0
2019-05-13 wip release 1.3
2019-06-17 ff v0.13c.p4
2019-06-17 ff v0.13c.p4 release
2019-06-21 yabios - zsdcc r11292
2019-06-30 V1.3 - EOFY
2019-07-12 add Frank
2019-07-12 add Klaus
2019-08-09 pcb - check and re-order
2019-08-11 yabios - defc interrupt locations
2019-08-11 yabios - reorder definitions
2019-08-13 yabios - revert asci defc deletion
2019-09-21 app - mandelbrot labels
2019-09-21 CP/M - MS-COBOL v4.65 - 60 Years Anniversary of COBOL
2019-09-21 CP/M - MS-COBOL v4.65 - 60 Year Anniversary of COBOL
2019-10-03 yaz180 - r1.4
2019-10-15 yabios - FatFS 0.14 & #1304
2019-10-26 readme - add I2C video link
2019-10-26 readme - add I2C video thumbnail
2019-10-26 readme - add I2C video remark
2019-11-02 yabios - minor fixes
2019-12-21 yabios - v1.5 2020
2019-12-21 yabios v1.5 2020
2019-12-21 cpm22 - recompile for yabios 1.5
2019-12-22 cpm22 - reinstate Rxflush
2019-12-22 yaz180 - v15 release
2019-12-31 yabios - ffconf update
2020-02-09 yabios - minor cleanup
2020-02-29 yabios -readme.md - freeRTOS
2020-03-14 yabios v1.6
2020-03-31 yabios - v1.6 refresh
2020-04-03 CP/M - update TE.COM to v1.4
2020-04-25 cpm22 - v2 drive config
2020-04-25 yabios v2.0
2020-04-26 yaz180 - release 2.0
2020-04-26 release - read.me
2020-04-27 Update readme.md
    Fix RAM banks available.
2020-04-30 cpm - 256 Sectors per Track
2020-05-01 cpm22 - dmac0 copies
2020-05-03 CP/M - BDOS LDI
2020-05-05 cpm - tidy BDOS
2020-05-05 Release 2.0
2020-05-06 cpm - bdos remove 8080isms
2020-05-06 cpm - bios hot cycle shaving
2020-05-07 cpm - hstalb fix - recover 1kB TPA
2020-05-10 cpm - PL/I 1.4 drive
2020-05-13 cpm - NZCOM distribution disk
2020-07-16 yabios - remove PUBLIC defs
2020-07-19 yabios - minor edits
2020-10-01 yabios & cpm - zsdcc r11877 & CCP optimisation
2020-12-02 yabios mv & sdcc 11940
2020-12-05 z180tool - update owners
2021-01-22 yabios - recompile with zsdcc 12017
2021-02-25 yabios 2.1 - opcode trap & zx0 compression
2021-03-01 CP/M - add SLR Tools and SLR Tools Plus (Z80ASM+ Rel 1.12, SLRNK+ Rel2.02)
2021-03-03 yabios 2.1 - release code
2021-03-04 yabios V2.1 hex
2021-04-06 update readme.md etc
2021-06-04 yabios - asci0 RTS flow control
2021-06-05 yabios - optimise RTS flow control
2021-06-05 introduce end-of-line normalisation
2021-06-08 yabios - comment typos
2021-06-09 yabios - recompile with zsdcc r12419 & #1811
2021-06-11 yabios - improve opcode trap
2021-06-12 yabios - improve _jp_far
2021-06-14 yabios - minimise critical instructions
2021-10-07 yabios - add SCCZ80 headers
2021-10-07 yabios - asci0 8n2 on next release
2022-01-27 cpm22 - whitespace and trivial
2022-03-08 Release 2.2 - zsdcc v4.2.0 recompile
2022-06-11 yabios - minor UI update
2022-06-12 cpm22 - update HiTech-C to Release 15
2022-07-10 CP/M - add TURBO Pascal v3.01
2022-08-22 yabios - simplify command token parsing - v2.2
2022-08-23 yabios - default FATFS drive 0:
2022-08-23 release - update readme for v2.2
2022-08-27 yabios - fix ls
2022-08-30 yabios - static FILEINFO
2022-09-12 yabios - add frag function
2022-11-13 yabios - update PIO definitions
2022-11-17 yabios - FatFs R0.15
2023-09-09 yabios - zsdcc 4.3.0 2023 refresh
2024-02-04 yabios - zsdcc 4.4.0 2024 refresh
2025-05-20 release - update for a v2.3 release
2025-06-25 CP/M - update entry and conio handling
2025-06-25 CP/M - fix comments
